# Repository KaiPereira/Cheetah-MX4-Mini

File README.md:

# Cheetah MX4 Mini Motherboard

The Cheetah MX4 Mini is a fully open source, powerful, yet affordable 3D printer motherboard! At just 80x90mm wide, it's an extremely compact motherboard with many cool features! This is one of the first PCB's I've ever created, so it might have some flaws.
## Custom Features
- 4 TMC stepstick drivers that support UART and SPI
- Sensorless and endstop homing configured using jumpers
- 3 Thermistor input connectors
- Support for parallel and serial LCD's and TFT displays
- 3 Fan output connectors
- Support for the BLTouch Probe (servo and probe connectors too)
- 2 High amperage heater outputs for a bed and miscellaneous
- Powerful STM32H743VIT6 LQFP100 MCU
- Support for USB-C and SD-Card printing
- 4x M3 grounded mounting holes
- Status and Power LEDs for programming
- 12/24V, 15A Input

## PCB Design

The Cheetah MX4 Mini is a 4 layer PCB with dedicated power and ground inner layers. Don't mind the messy PCB/schematic, it was one of my first boards ;) 

It's built off the STM32H series MCU to support every function you need for a printer. It's got many protection circuits, good decoupling, and is designed around high current inputs.

To power it, you can supply either USB-C for development, or a 12/24V PSU to drive the motors and all the other parts like the drivers.

You can upload prints via USB-C or SD Card, with support for UART and SPI TMC drivers, and you can hot-swap the motor drivers for maximum control.

## Firmware

The Cheetah MX4 Mini uses an STM32H743VIT6 MCU, so it has support for both Marlin, Klipper and most other 3D printer firmwares!

To get started, you can upload firmware to the onboard flash using the dedicated boot and reset pins!

More information on firmware *coming soon...*

## BOM (Bill of Materials)

I've created a BOM for JLCPCB and a general footprint BOM if you want to get PCBA from somewhere else like PCBWay or something.

The JLCPCB BOM is actually relatively cheap, coming in at about $150 for all 5 boards which I was pretty impressed with!

The LCSC BOM costs about $20 for the actual parts and then shipping will be about $20.

You can find the JLCPCB BOM [here](/production/BOM_JLCPCB.csv).

The LCSC BOM [here](/production/BOM_LCSC.csv)

The general footprint BOM is [here](/production/BOM.csv).

There's also a pick and place formatted for [JLCPCB](/production/CPL_JLCPCB.csv) and a general one if you're using a different platform [here](/production/CPL.csv).

## Credits

Thanks so much to @Fisheiyy and for the folks on Reddit for reviewing and helping me with the board, without them, this board probably would have never worked or come to fruition! Thanks also to Hackclub, specifically @qcoral and @acornitum for running [Highway](https://highway.hackclub.com/) which sponsored the board!

## License

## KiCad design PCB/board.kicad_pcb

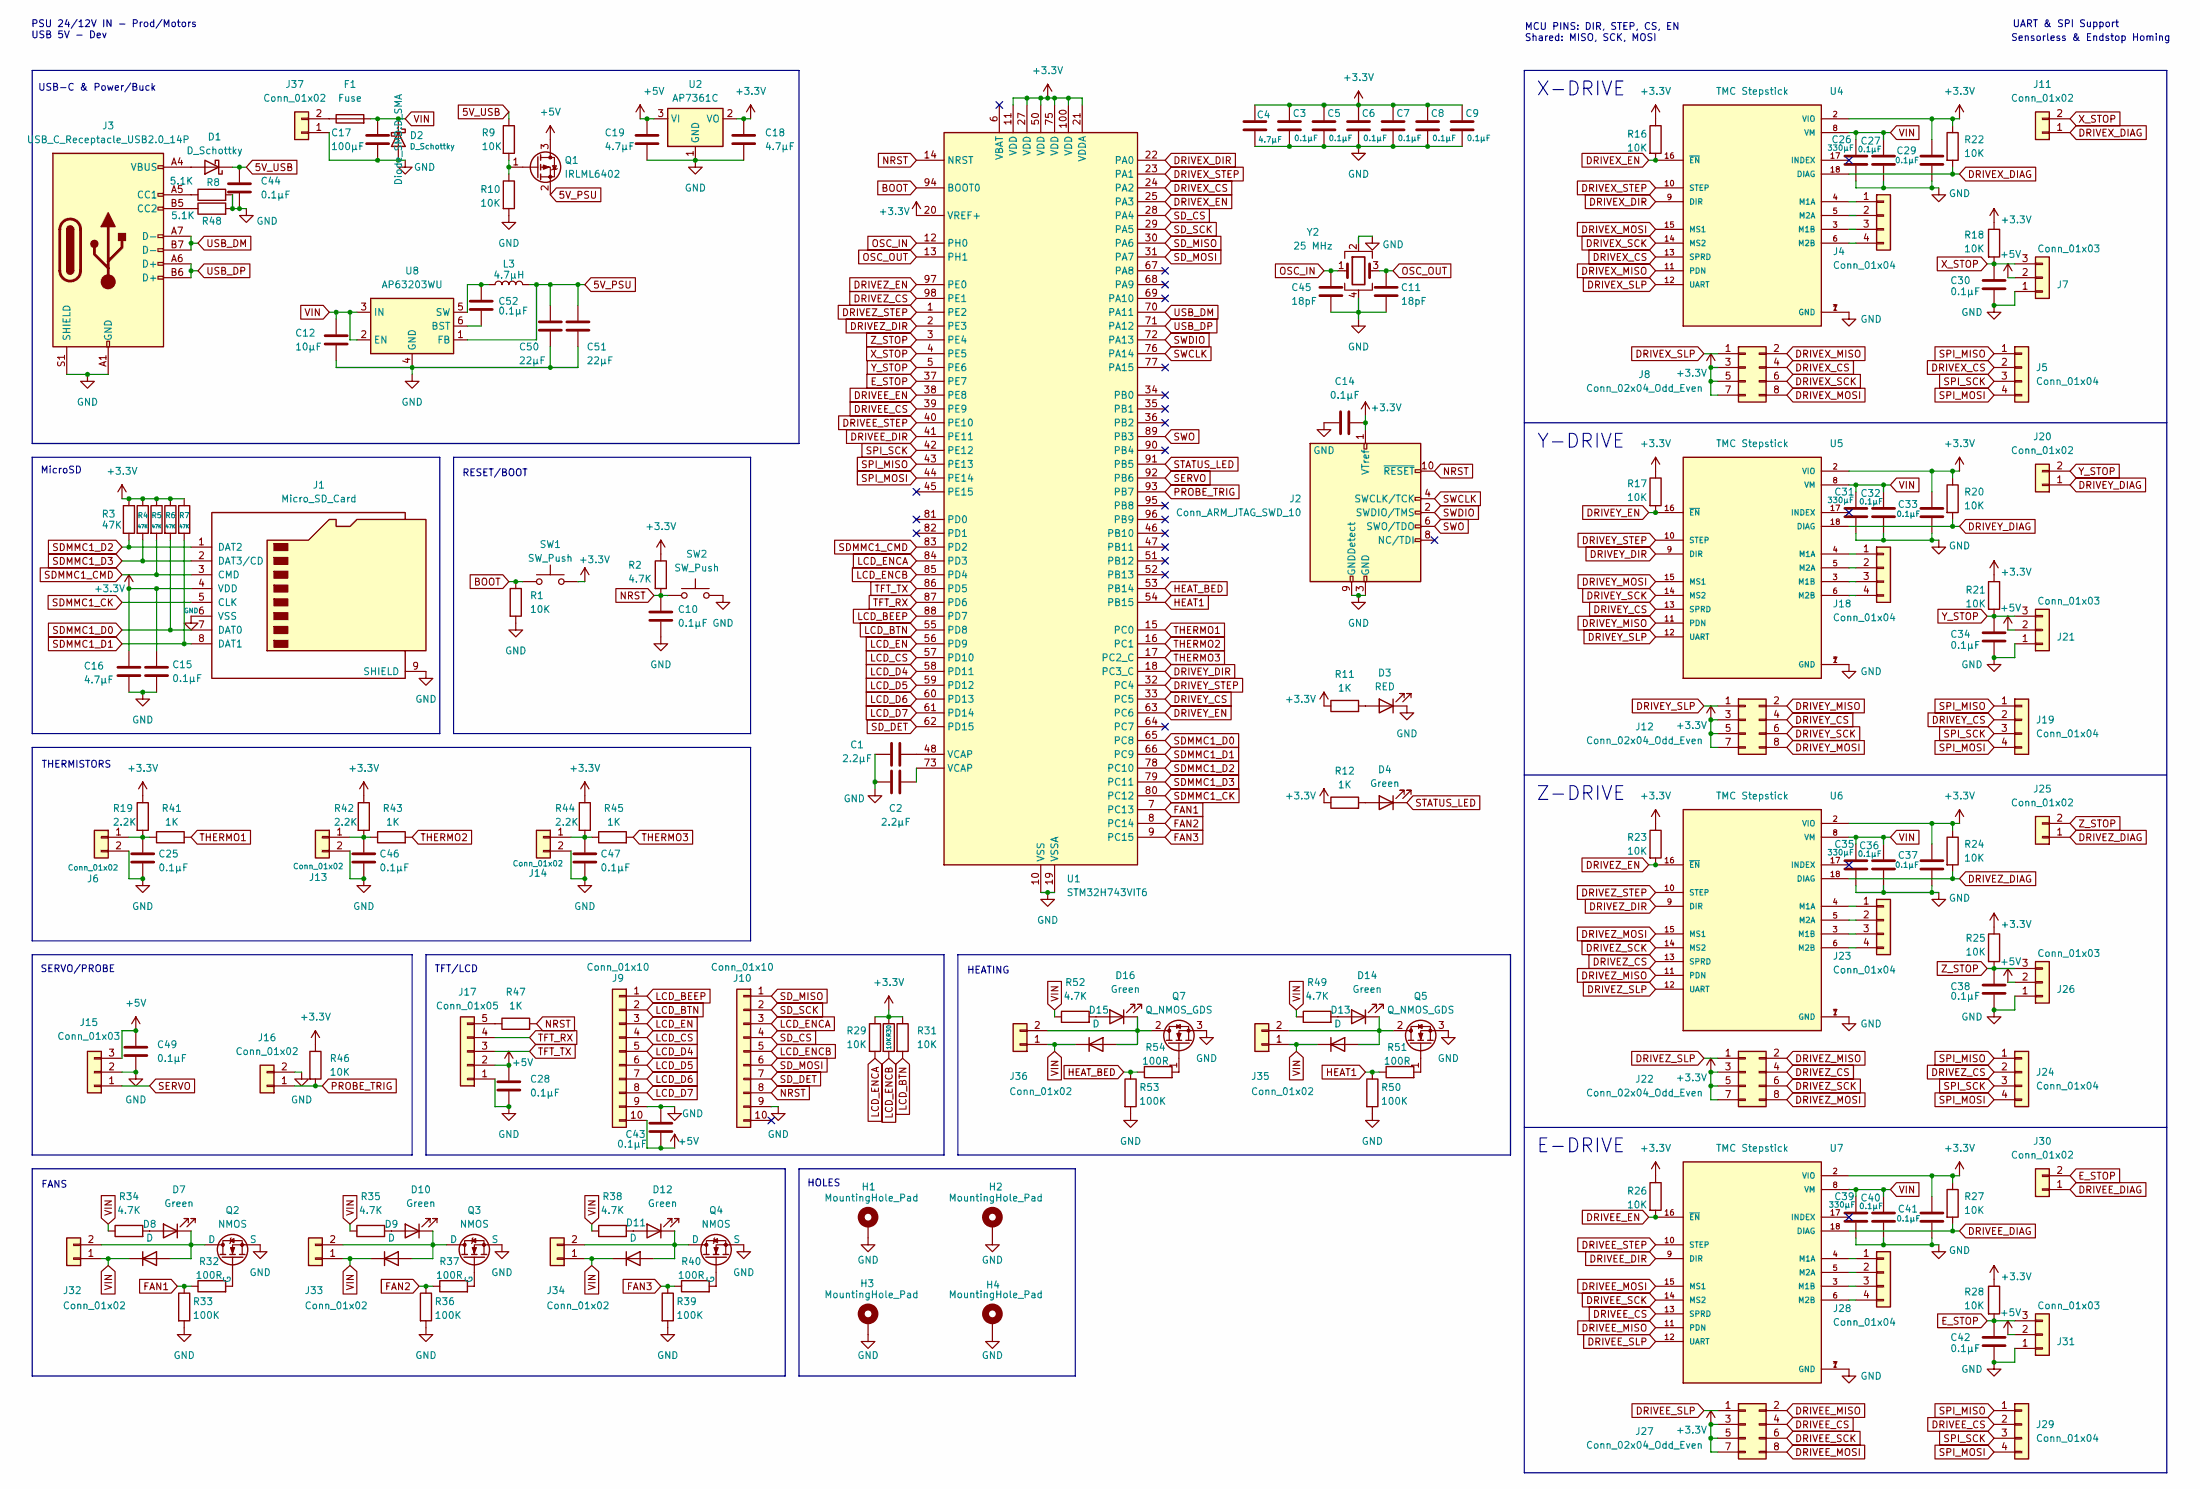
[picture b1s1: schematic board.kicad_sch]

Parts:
C1, C2: 2.2µF; C_0805_2012Metric
C3, C5, C6, C7, C8, C9, C10, C14, C15, C25, C27, C28, C29, C30, C32, C33, C34, C36, C37, C38, C40, C41, C42, C43, C44, C46, C47, C49, C52: 0.1µF; C_0603_1608Metric
C4, C16, C18, C19: 4.7µF; C_0805_2012Metric
C11, C45: 18pF; C_0603_1608Metric
C12: 10µF; C_0805_2012Metric
C17: 100µF; CP_Radial_D6.3mm_P2.50mm
C26, C31, C35, C39: 330µF; CP_Radial_D8.0mm_P3.50mm
C50, C51: 22µF; C_0805_2012Metric
D1: D_Schottky; D_SOD-123
D2: D_Schottky; D_SMA
D3: RED; LED_0805_2012Metric
D4, D7, D10, D12, D14, D16: Green; LED_0805_2012Metric
D8, D9, D11, D13, D15: D; D_SOD-123
F1: Fuse; Fuse_Blade_Mini_directSolder
H1, H2, H3, H4: MountingHole_Pad; MountingHole_3.2mm_M3_Pad_TopBottom
J1: Micro_SD_Card; microSD_HC_Hirose_DM3AT-SF-PEJM5
J2: Conn_ARM_JTAG_SWD_10; PinHeader_2x05_P1.27mm_Vertical
J3: USB_C_Receptacle_USB2.0_14P; USB_C_Receptacle_HRO_TYPE-C-31-M-12
J4, J18, J23, J28: Conn_01x04; JST_XH_B4B-XH-AM_1x04_P2.50mm_Vertical
J5, J19, J24, J29: Conn_01x04; PinHeader_1x04_P2.00mm_Vertical
J6, J13, J14, J32, J33, J34: Conn_01x02; JST_PH_B2B-PH-K_1x02_P2.00mm_Vertical
J7, J21, J26, J31: Conn_01x03; JST_XH_B3B-XH-A_1x03_P2.50mm_Vertical
J8, J12, J22, J27: Conn_02x04_Odd_Even; PinHeader_2x04_P2.00mm_Vertical
J9, J10: Conn_01x10; IDC-Header_2x05_P2.54mm_Vertical
J11, J16, J20, J25, J30: Conn_01x02; PinHeader_1x02_P2.54mm_Vertical
J15: Conn_01x03; PinHeader_1x03_P2.54mm_Vertical
J17: Conn_01x05; JST_XH_B5B-XH-AM_1x05_P2.50mm_Vertical
J35, J36, J37: Conn_01x02; TerminalBlock_Phoenix_MKDS-1,5-2-5.08_1x02_P5.08mm_Horizont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
L3: 4.7µH; L_Wuerth_HCM-7070
Q1: IRLML6402; SOT-23
Q2, Q3, Q4: NMOS; SOT-23-3
Q5, Q7: Q_NMOS_GDS; TO-252-3_TabPin2
R1, R9, R10, R16, R17, R18, R21, R23, R25, R26, R28, R29, R30, R31, R46: 10K; R_0603_1608Metric
R2, R34, R35, R38, R49, R52: 4.7K; R_0603_1608Metric
R3, R4, R5, R6, R7: 47K; R_0603_1608Metric
R8, R48: 5.1K; R_0603_1608Metric
R11, R12, R41, R43, R45, R47: 1K; R_0603_1608Metric
R19, R42, R44: 2.2K; R_0603_1608Metric
R20, R22, R24, R27: 10K; R_0805_2012Metric
R32, R37, R40, R51, R54: 100R; R_0603_1608Metric
R33, R36, R39, R50, R53: 100K; R_0603_1608Metric
SW1, SW2: SW_Push; SW_Push_1P1T_NO_CK_KMR2
U1: STM32H743VIT6; LQFP-100_14x14mm_P0.5mm
U2: AP7361C; SOT-223-3_TabPin2
U4, U5, U6, U7: TMC Stepstick; PARTREV 1.20
U8: AP63203WU; TSOT-23-6
Y2: 25 MHz; Crystal_SMD_3225-4Pin_3.2x2.5mm

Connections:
5V_PSU: C50.1, C51.1, L3.2, Q1.2 (S), U8.1 (FB)
5V_USB: C44.1, D1.1 (K), R9.1
+3.3V: C3.1, C4.1, C5.1, C6.1, C7.1, C8.1, C9.1, C14.2, C15.1, C16.1, C18.1, C29.1, C33.1, C37.1, C41.1, J1.4 (VDD), J2.1 (VTref), J8.3, J8.5, J8.7, J12.3, J12.5, J12.7, J22.3, J22.5, J22.7, J27.3, J27.5, J27.7, R2.1, R3.1, R4.1, R5.1, R6.1, R7.1, R11.1, R12.1, R16.1, R17.1, R18.1, R19.1, R20.1, R21.1, R22.1, R23.1, R24.1, R25.1, R26.1, R27.1, R28.1, R29.1, R30.1, R31.1, R42.1, R44.1, R46.1, SW1.2, U1.11 (VDD), U1.20 (VREF+), U1.21 (VDDA), U1.27 (VDD), U1.50 (VDD), U1.75 (VDD), U1.100 (VDD), U2.2 (VO), U4.2 (VIO), U5.2 (VIO), U6.2 (VIO), U7.2 (VIO)
+5V: C19.1, C28.1, C43.2, C49.1, J7.2, J9.10, J15.3, J17.2, J21.2, J26.2, J31.2, Q1.3 (D), U2.3 (VI)
BOOT: R1.1, SW1.1, U1.94 (BOOT0)
DRIVEE_CS: J27.4, J29.2, U1.39 (PE9), U7.13 (SPRD)
DRIVEE_DIAG: J30.1, R27.2, U7.18 (DIAG)
DRIVEE_DIR: U1.41 (PE11), U7.9 (DIR)
DRIVEE_EN: R26.2, U1.38 (PE8), U7.16 (~EN)
DRIVEE_MISO: J27.2, U7.11 (PDN)
DRIVEE_MOSI: J27.8, U7.15 (MS1)
DRIVEE_SCK: J27.6, U7.14 (MS2)
DRIVEE_SLP: J27.1, U7.12 (UART)
DRIVEE_STEP: U1.40 (PE10), U7.10 (STEP)
DRIVEX_CS: J5.2, J8.4, U1.24 (PA2), U4.13 (SPRD)
DRIVEX_DIAG: J11.1, R22.2, U4.18 (DIAG)
DRIVEX_DIR: U1.22 (PA0), U4.9 (DIR)
DRIVEX_EN: R16.2, U1.25 (PA3), U4.16 (~EN)
DRIVEX_MISO: J8.2, U4.11 (PDN)
DRIVEX_MOSI: J8.8, U4.15 (MS1)
DRIVEX_SCK: J8.6, U4.14 (MS2)
DRIVEX_SLP: J8.1, U4.12 (UART)
DRIVEX_STEP: U1.23 (PA1), U4.10 (STEP)
DRIVEY_CS: J12.4, J19.2, U1.33 (PC5), U5.13 (SPRD)
DRIVEY_DIAG: J20.1, R20.2, U5.18 (DIAG)
DRIVEY_DIR: U1.18 (PC3_C), U5.9 (DIR)
DRIVEY_EN: R17.2, U1.63 (PC6), U5.16 (~EN)
DRIVEY_MISO: J12.2, U5.11 (PDN)
DRIVEY_MOSI: J12.8, U5.15 (MS1)
DRIVEY_SCK: J12.6, U5.14 (MS2)
DRIVEY_SLP: J12.1, U5.12 (UART)
DRIVEY_STEP: U1.32 (PC4), U5.10 (STEP)
DRIVEZ_CS: J22.4, J24.2, U1.98 (PE1), U6.13 (SPRD)
DRIVEZ_DIAG: J25.1, R24.2, U6.18 (DIAG)
DRIVEZ_DIR: U1.2 (PE3), U6.9 (DIR)
DRIVEZ_EN: R23.2, U1.97 (PE0), U6.16 (~EN)
DRIVEZ_MISO: J22.2, U6.11 (PDN)
DRIVEZ_MOSI: J22.8, U6.15 (MS1)
DRIVEZ_SCK: J22.6, U6.14 (MS2)
DRIVEZ_SLP: J22.1, U6.12 (UART)
DRIVEZ_STEP: U1.1 (PE2), U6.10 (STEP)
E_STOP: C42.1, J30.2, J31.3, R28.2, U1.37 (PE7)
FAN1: R32.1, R33.1, U1.7 (PC13)
FAN2: R36.1, R37.1, U1.8 (PC14)
FAN3: R39.1, R40.1, U1.9 (PC15)
GND: C1.1, C2.1, C3.2, C4.2, C5.2, C6.2, C7.2, C8.2, C9.2, C10.2, C11.1, C12.2, C14.1, C15.2, C16.2, C17.2, C18.2, C19.2, C25.2, C26.2, C27.2, C28.2, C29.2, C30.2, C31.2, C32.2, C33.2, C34.2, C35.2, C36.2, C37.2, C38.2, C39.2, C40.2, C41.2, C42.2, C43.1, C44.2, C45.1, C46.2, C47.2, C49.2, C50.2, C51.2, D2.2 (A), D3.1 (K), H1.1, H2.1, H3.1, H4.1, J1.6 (VSS), J1.9 (SHIELD), J2.3 (GND), J2.5 (GND), J2.9 (GNDDetect), J3.A1 (GND), J3.A12 (GND), J3.B1 (GND), J3.B12 (GND), J3.S1 (SHIELD), J6.2, J7.1, J9.9, J10.9, J13.2, J14.2, J15.2, J16.2, J17.1, J21.1, J26.1, J31.1, J37.1, Q2.3 (S), Q3.3 (S), Q4.3 (S), Q5.3 (S), Q7.3 (S), R1.2, R8.2, R10.2, R33.2, R36.2, R39.2, R48.2, R50.2, R53.2, SW2.2, U1.10 (VSS), U1.19 (VSSA), U1.26 (VSS), U1.49 (VSS), U1.74 (VSS), U1.99 (VSS), U2.1 (GND), U4.1 (GND), U4.7 (GND), U5.1 (GND), U5.7 (GND), U6.1 (GND), U6.7 (GND), U7.1 (GND), U7.7 (GND), U8.4 (GND), Y2.2, Y2.4
HEAT1: R50.1, R51.1, U1.54 (PB15)
HEAT_BED: R53.1, R54.1, U1.53 (PB14)
LCD_BEEP: J9.1, U1.88 (PD7)
LCD_BTN: J9.2, R31.2, U1.55 (PD8)
LCD_CS: J9.4, U1.57 (PD10)
LCD_D4: J9.5, U1.58 (PD11)
LCD_D5: J9.6, U1.59 (PD12)
LCD_D6: J9.7, U1.60 (PD13)
LCD_D7: J9.8, U1.61 (PD14)
LCD_EN: J9.3, U1.56 (PD9)
LCD_ENCA: J10.3, R29.2, U1.84 (PD3)
LCD_ENCB: J10.5, R30.2, U1.85 (PD4)
NRST: C10.1, J2.10 (~RESET), J10.8, R2.2, R47.2, SW2.1, U1.14 (NRST)
unnamed: C1.2, U1.48 (VCAP)
unnamed: C2.2, U1.73 (VCAP)
unnamed: D1.2 (A), J3.A4 (VBUS), J3.A9 (VBUS), J3.B4 (VBUS), J3.B9 (VBUS)
unnamed: D3.2 (A), R11.2
unnamed: D4.2 (A), R12.2
unnamed: D7.2 (A), R34.2
unnamed: D7.1 (K), D8.2 (A), J32.2, Q2.1 (D)
unnamed: D10.2 (A), R35.2
unnamed: D9.2 (A), D10.1 (K), J33.2, Q3.1 (D)
unnamed: D11.2 (A), D12.1 (K), J34.2, Q4.1 (D)
unnamed: D12.2 (A), R38.2
unnamed: D13.2 (A), D14.1 (K), J35.2, Q5.2 (D)
unnamed: D14.2 (A), R49.2
unnamed: D15.2 (A), D16.1 (K), J36.2, Q7.2 (D)
unnamed: D16.2 (A), R52.2
unnamed: J3.A5 (CC1), R8.1
unnamed: J3.B5 (CC2), R48.1
unnamed: J4.1, U4.4 (M1A)
unnamed: J4.2, U4.5 (M2A)
unnamed: J4.3, U4.3 (M1B)
unnamed: J4.4, U4.6 (M2B)
unnamed: C25.1, J6.1, R19.2, R41.1
unnamed: C46.1, J13.1, R42.2, R43.1
unnamed: C47.1, J14.1, R44.2, R45.1
unnamed: J17.5, R47.1
unnamed: J18.1, U5.4 (M1A)
unnamed: J18.2, U5.5 (M2A)
unnamed: J18.3, U5.3 (M1B)
unnamed: J18.4, U5.6 (M2B)
unnamed: J23.1, U6.4 (M1A)
unnamed: J23.2, U6.5 (M2A)
unnamed: J23.3, U6.3 (M1B)
unnamed: J23.4, U6.6 (M2B)
unnamed: J28.1, U7.4 (M1A)
unnamed: J28.2, U7.5 (M2A)
unnamed: J28.3, U7.3 (M1B)
unnamed: J28.4, U7.6 (M2B)
unnamed: F1.1, J37.2
unnamed: Q1.1 (G), R9.2, R10.1
unnamed: Q2.2 (G), R32.2
unnamed: Q3.2 (G), R37.2
unnamed: Q4.2 (G), R40.2
unnamed: Q5.1 (G), R51.2
unnamed: Q7.1 (G), R54.2
unnamed: C52.2, U8.6 (BST)
unnamed: C52.1, L3.1, U8.5 (SW)
OSC_IN: C45.2, U1.12 (PH0), Y2.1
OSC_OUT: C11.2, U1.13 (PH1), Y2.3
PROBE_TRIG: J16.1, R46.2, U1.93 (PB7)
SDMMC1_CK: J1.5 (CLK), U1.80 (PC12)
SDMMC1_CMD: J1.3 (CMD), R5.2, U1.83 (PD2)
SDMMC1_D0: J1.7 (DAT0), R6.2, U1.65 (PC8)
SDMMC1_D1: J1.8 (DAT1), R7.2, U1.66 (PC9)
SDMMC1_D2: J1.1 (DAT2), R3.2, U1.78 (PC10)
SDMMC1_D3: J1.2 (DAT3/CD), R4.2, U1.79 (PC11)
SD_CS: J10.4, U1.28 (PA4)
SD_DET: J10.7, U1.62 (PD15)
SD_MISO: J10.1, U1.30 (PA6)
SD_MOSI: J10.6, U1.31 (PA7)
SD_SCK: J10.2, U1.29 (PA5)
SERVO: J15.1, U1.92 (PB6)
SPI_MISO: J5.1, J19.1, J24.1, J29.1, U1.43 (PE13)
SPI_MOSI: J5.4, J19.4, J24.4, J29.4, U1.44 (PE14)
SPI_SCK: J5.3, J19.3, J24.3, J29.3, U1.42 (PE12)
STATUS_LED: D4.1 (K), U1.91 (PB5)
SWCLK: J2.4 (SWCLK/TCK), U1.76 (PA14)
SWDIO: J2.2 (SWDIO/TMS), U1.72 (PA13)
SWO: J2.6 (SWO/TDO), U1.89 (PB3)
TFT_RX: J17.4, U1.87 (PD6)
TFT_TX: J17.3, U1.86 (PD5)
THERMO1: R41.2, U1.15 (PC0)
THERMO2: R43.2, U1.16 (PC1)
THERMO3: R45.2, U1.17 (PC2_C)
USB_DM: J3.A7 (D-), J3.B7 (D-), U1.70 (PA11)
USB_DP: J3.A6 (D+), J3.B6 (D+), U1.71 (PA12)
VIN: C12.1, C17.1, C26.1, C27.1, C31.1, C32.1, C35.1, C36.1, C39.1, C40.1, D2.1 (K), D8.1 (K), D9.1 (K), D11.1 (K), D13.1 (K), D15.1 (K), F1.2, J32.1, J33.1, J34.1, J35.1, J36.1, R34.1, R35.1, R38.1, R49.1, R52.1, U4.8 (VM), U5.8 (VM), U6.8 (VM), U7.8 (VM), U8.2 (EN), U8.3 (IN)
X_STOP: C30.1, J7.3, J11.2, R18.2, U1.4 (PE5)
Y_STOP: C34.1, J20.2, J21.3, R21.2, U1.5 (PE6)
Z_STOP: C38.1, J25.2, J26.3, R25.2, U1.3 (PE4)

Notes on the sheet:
PSU 24/12V IN - Prod/Motors USB 5V - Dev
MicroSD
Y-DRIVE
UART & SPI Support
SERVO/PROBE
HOLES
Z-DRIVE
THERMISTORS
USB-C & Power/Buck
X-DRIVE
TFT/LCD
MCU PINS: DIR, STEP, CS, EN Shared: MISO, SCK, MOSI
HEATING
E-DRIVE
Sensorless & Endstop Homing
FANS
RESET/BOOT

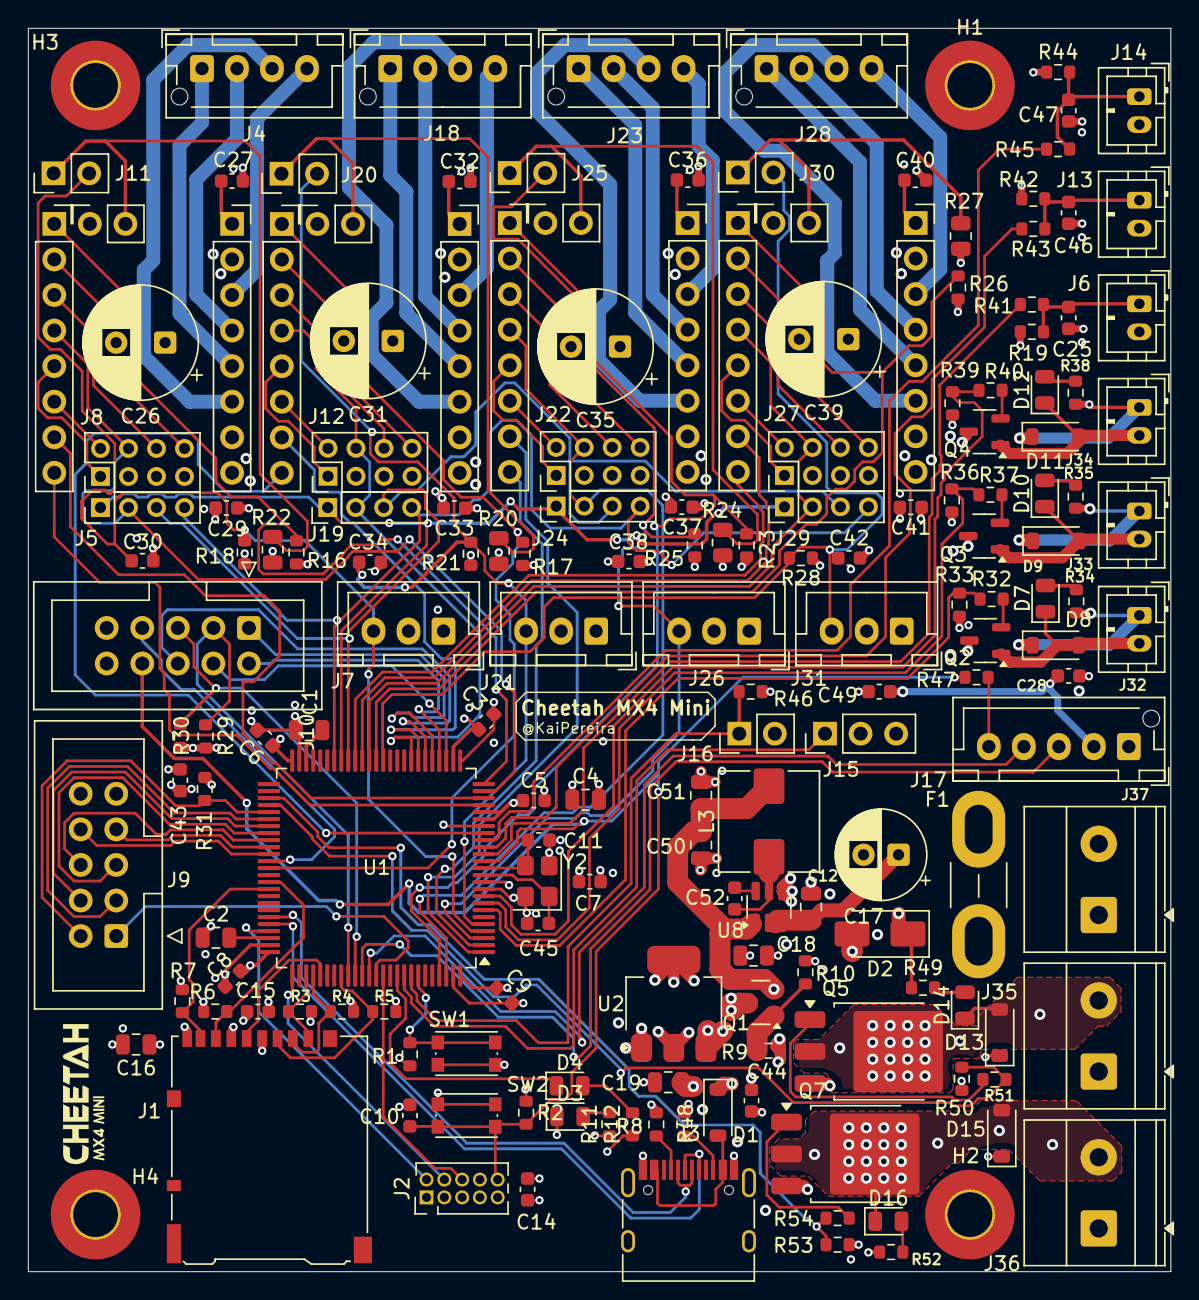
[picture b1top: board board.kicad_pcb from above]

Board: 4 copper layers, 81.6 x 88.8 mm, 169 parts (0 on the bottom side), 138 nets.

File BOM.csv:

"Id";"Designator";"Footprint";"Quantity";"Designation";"Supplier and ref";
1;"C51,C50";"C_0805_2012Metric";2;"22µF";;;
2;"R33,R39,R36,R50,R53";"R_0603_1608Metric";5;"100K";;;
3;"Q7,Q5";"TO-252-3_TabPin2";2;"Q_NMOS_GDS";;;
4;"C45,C11";"C_0603_1608Metric";2;"18pF";;;
5;"C15,C27,C7,C43,C40,C6,C32,C46,C28,C49,C8,C29,C3,C36,C10,C52,C37,C33,C30,C25,C38,C42,C34,C14,C9,C41,C47,C44,C5";"C_0603_1608Metric";29;"0.1µF";;;
6;"R10,R26,R25,R18,R21,R16,R1,R30,R28,R29,R31,R46,R9,R17,R23";"R_0603_1608Metric";15;"10K";;;
7;"J2";"PinHeader_2x05_P1.27mm_Vertical_SMD";1;"Conn_ARM_JTAG_SWD_10";;;
8;"J19,J29,J24,J5";"PinHeader_1x04_P2.00mm_Vertical";4;"Conn_01x04";;;
9;"J12,J27,J22,J8";"PinHeader_2x04_P2.00mm_Vertical";4;"Conn_02x04_Odd_Even";;;
10;"C19,C18,C16,C4";"C_0805_2012Metric";4;"4.7µF";;;
11;"J4,J28,J18,J23";"JST_XH_B4B-XH-AM_1x04_P2.50mm_Vertical";4;"Conn_01x04";;;
12;"SW2,SW1";"SW_Push_1P1T_NO_CK_KMR2";2;"SW_Push";;;
13;"R49,R2,R34,R35,R38,R52";"R_0603_1608Metric";6;"4.7K";;;
14;"L3";"L_Wuerth_HCM-7070";1;"4.7µH";;;
15;"J11,J30,J20,J16,J25";"PinHeader_1x02_P2.54mm_Vertical";5;"Conn_01x02";;;
16;"D10,D7,D16,D12,D14";"R_0805_2012Metric";5;"Green";;;
17;"R40,R51,R37,R32,R54";"R_0603_1608Metric";5;"100R";;;
18;"U2";"SOT-223-3_TabPin2";1;"AP7361C";;;
19;"U5,U7,U4,U6";"TMC Stepstick";4;"TMC Stepstick";;;
20;"D1";"D_SOD-123";1;"D_Schottky";;;
21;"R20,R27,R22,R24";"R_0805_2012Metric";4;"10K";;;
22;"J13,J14,J33,J6,J34,J32";"JST_PH_B2B-PH-K_1x02_P2.00mm_Vertical";6;"Conn_01x02";;;
23;"U1";"LQFP-100_14x14mm_P0.5mm";1;"STM32H743VITx";;;
24;"R7,R3,R4,R6,R5";"R_0603_1608Metric";5;"47K";;;
25;"R47,R45,R43,R41";"R_0603_1608Metric";4;"1K";;;
26;"Q3,Q4,Q2";"SOT-23-3";3;"NMOS";;;
27;"U8";"TSOT-23-6";1;"AP63203WU";;;
28;"J36,J37,J35";"TerminalBlock_Phoenix_MKDS-1,5-2-5.08_1x02_P5.08mm_Horizontal";3;"Conn_01x02";;;
29;"D2";"D_SMA";1;"D_Schottky";;;
30;"C39,C31,C35,C26";"CP_Radial_D8.0mm_P3.50mm";4;"330µF";;;
31;"D13,D15,D9,D8,D11";"D_SOD-123";5;"D";;;
32;"J26,J7,J31,J21";"JST_XH_B3B-XH-A_1x03_P2.50mm_Vertical";4;"Conn_01x03";;;
33;"J17";"JST_XH_B5B-XH-AM_1x05_P2.50mm_Vertical";1;"Conn_01x05";;;
34;"R48,R8";"R_0603_1608Metric";2;"5.1K";;;
35;"F1";"Fuse_Blade_Mini_directSolder";1;"Fuse";;;
36;"J1";"microSD_HC_Hirose_DM3AT-SF-PEJM5";1;"Micro_SD_Card";;;
37;"R44,R42,R19";"R_0603_1608Metric";3;"2.2K";;;
38;"J15";"PinHeader_1x03_P2.54mm_Vertical";1;"Conn_01x03";;;
39;"J3";"USB_C_Receptacle_HRO_TYPE-C-31-M-12";1;"USB_C_Receptacle_USB2.0_14P";;;
40;"C12";"C_0805_2012Metric";1;"10µF";;;
41;"J9,J10";"IDC-Header_2x05_P2.54mm_Vertical";2;"Conn_01x10";;;
42;"C17";"CP_Radial_D6.3mm_P2.50mm";1;"100µF";;;
43;"C2,C1";"C_0805_2012Metric";2;"2.2µF";;;
44;"Y2";"Crystal_SMD_3225-4Pin_3.2x2.5mm";1;"25 MHz";;;
45;"Q1";"SOT-23";1;"IRLML6402";;;

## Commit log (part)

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2025-07-20 started project, this is probably a bad idea lol
2025-07-20 everything so far
2025-07-21 added PCB files again
2025-07-21 started the schematic, I still think this is a horrible idea, but it's going to be so cool
2025-07-21 adding decoupling caps to VDD
2025-07-21 adding boot and fixed the decoupling
2025-07-21 danny helped me with my PCB :D
2025-07-21 working on NRST
2025-07-21 separate the boot/reset schematic into a little box!
2025-07-21 added crystal oscillator
2025-07-21 added clock stuff and updated my journal
2025-07-21 adding ferrite bead to VDD
2025-07-21 adding my SWD debugger headers, I think I'm using the wrong symbol though
2025-07-22 adding the SD card
2025-07-22 connected shield to GND and updated journal with SD card
2025-07-22 adding usb-c in progress
2025-07-22 usb-c is done I think
2025-07-22 forgot to save USB-C, but I did that, and I also wrote about it in the journal
2025-07-22 saved
2025-07-22 formatting the schematic a bit better
2025-07-22 adding psu
2025-07-22 psu stuff
2025-07-22 added psu circuit
2025-07-22 added buck converter
2025-07-22 adding journal for PSU and buck converter
2025-07-23 added the new buck converter but the schematic looks a tad messy and the value's aren't in eyt
2025-07-23 switching power net labels to power labels
2025-07-23 added new buck converter
2025-07-23 added new blog for the buck converter
2025-07-23 added LDO
2025-07-24 P-Mosfet for PSU/USB switching and added the LDO
2025-07-24 added a new TMC symbol from snapeda
2025-07-24 added stepstick driver, I think it's fine, but I'm not too sure
2025-07-24 re-organized the schematic and bit more and did the journal for the stepper
2025-07-24 added the endstop, but now I have to implement both sensorless and endstop home
2025-07-24 added endstop connectors and started working on footprints and stuff which was dumb not to do initially, also already added the journal log
2025-07-24 fixing the TMC2209 stepstick, I was wiring it like the IC, not the module for some reason and it was a bit off in general
2025-07-24 added decoupling caps to power pins on drivers
2025-07-24 added some thermistor stuff and re-organized a bit
2025-07-25 fixed the UART on the drivers
2025-07-25 sd card peripheral was messed up for some reason
2025-07-25 added all motor drivers in (x, y, z, e0)
2025-07-25 updated the journal on adding all the motor drivers in
2025-07-25 added in the first thermistor with protection
2025-07-25 adding all the thermistors
2025-07-25 adding the journal for the rest of the thermistors
2025-07-25 added the servo connector
2025-07-25 added probe stuff
2025-07-25 fixed some dumb language mistakes
2025-07-25 fixed usb cc pin not pulled down and lower bulk capacitance cap on the PSU
2025-07-25 fixing capacitors on the motor drivers, removed the other drivers while making edits
2025-07-25 fixed pullups on thermistors
2025-07-26 finally fixed the UART on my drivers! Thanks salmon :D
2025-07-26 added some SPI peripherals on
2025-07-26 working on more SPI stuff, working on jumpers
2025-07-26 I might crash out from SPI but this MIGHT be fine?
2025-07-26 refining the SPI a bit
2025-07-26 added all the drivers, but haven't named them yet
2025-07-26 kind of going insane, but I can't figure out how UART is getting a signal??
2025-07-27 added SPI to journal
2025-07-27 adding TFT to journal and fixing it up on the schematic
2025-07-27 adding the SPI/sd card display support
2025-07-27 added some stuff
2025-07-27 wired up some more stuff for the LCD's
2025-07-27 re-doing some driver pins because I keep on messing them up
2025-07-27 adding the endstop jumper to switch between sensorless and endstop
2025-07-27 almost everything wired on the TMC drivers
2025-07-27 some more formatting, almost done adding all the io's for the drivers
2025-07-27 that might be all the labels in the right spots for the drivers?
2025-07-27 updated the journal with all the stuff I did
2025-07-27 some more journaling stuff and pullups on LCD
2025-07-27 updated the journal and added some decoupling to LCD's
2025-07-27 working on fan
2025-07-27 added fans to journal
2025-07-27 added the heating outputs
2025-07-27 added the journal for the heating elements
2025-07-27 footprints for usb
2025-07-27 added footprints to the PSU
2025-07-27 footprints for psu
2025-07-27 sd card footprints
2025-07-27 added the footprints for the thermistors
2025-07-27 most of the capacitors using assign footprints
2025-07-27 some more footprints
2025-07-27 A LOT more footprint stuff
2025-07-28 even more footprints
2025-07-28 more footpritns, I should've done this while making the schematic...
2025-07-28 adding some more footprints
2025-07-28 all the driver connectors
2025-07-28 ALL the footprints except for the TMC stepsticks
2025-07-28 formatted the entire schematic much more nicely
2025-07-28 added all the stuff
2025-07-28 added journal for footprint
2025-07-28 added TMC footprint to the drivers
2025-07-28 changed some footprints to handle the loads
2025-07-28 fixing the footprint for the motor drivers
2025-07-28 fixed all the connectors except the LCD/TFT ones
2025-07-29 added the display connectors, finally!
2025-07-29 simplifying the BOM
2025-07-29 cleaner up some stuff, this would be a good commit to revert too
2025-07-29 moving the fuse before cap and diode
2025-07-29 making the diodes less overkill
2025-07-29 started working on the PCB
2025-07-29 working on the PCB!
2025-07-29 currently aligning all the parts for the pcb
2025-07-29 organized thermistors
2025-07-29 boot/reset and power organization
2025-07-29 everything organized on the board together, now I just have to precisely put it on, but I gotta figure out the screens first
2025-07-29 updated sd card, at least I think that was the change?
2025-07-29 changed the buttons
2025-07-29 switched symbol to receptacle instead of plug for usb-c
2025-07-29 started organizing the mcu more precisely
2025-07-29 fixed the crystal pins
2025-07-29 fixed up the mcu footprint some more
2025-07-29 added the current pcb stuff to the journal
2025-07-29 fixing the connector size on the UART/SPI toggle
2025-07-29 starting to organize the drivers nicely
2025-07-29 third driver
2025-07-29 fourth driver
2025-07-29 aligned all the motor drivers together
2025-07-29 added the driver alignement to journal
2025-07-29 lots of organizing the power and displays
2025-07-29 hopping off cuz it's 3am...
2025-07-29 fixed the buck converter
2025-07-29 new LDO and fixed decoup
2025-07-29 don't go to this commit, can't figure out 5V mosfet switching?
2025-07-29 added the power switching
2025-07-29 schematic looks golden now!
2025-07-29 added the schematic changes to the journal
2025-07-30 organizing everything into a more coherent board
2025-07-30 much better organization of the pcb
2025-07-30 organized fan connectors
2025-07-30 heaters
2025-07-30 all components place all organized
2025-07-30 added the organization stuff to the journal
2025-07-30 re-oriented, this is a good version to go to
2025-07-30 starting to compress everything now, motor drivers and mcu down
2025-07-30 compressing stuff
2025-07-30 compressing even more stuff, specifically the power stuff
2025-07-30 some major changes to placement
2025-07-30 trying a slightly different layout
2025-07-30 updated journal, but I need to fix the NMOS on the heaters
2025-07-30 changing the FET/Mosfet
2025-07-30 forgot to save board
2025-07-30 everything is on nicely, but I may or may not have forgotten mounting holes
2025-07-30 the board is almost ready to route! Good place to backup too
2025-07-30 fixed the mosfets on the heaters
2025-07-31 adding mounting holes
2025-07-31 first round of mounting holes
2025-07-31 ALL mounting holes placed down
2025-07-31 fine tuning some stuff
2025-07-31 some journal stuff and starting the routing
2025-07-31 started to via all the grounds down
2025-07-31 organized like over half the silkscreen
2025-07-31 progress so far
2025-07-31 started routing some stuff
2025-07-31 added some more routes
2025-07-31 lots more wiring
2025-07-31 filled the heaters a bit
2025-07-31 update journal for the routing
2025-07-31 routing the drivers
2025-07-31 routed a display and more stuff on the drivers + journal
2025-07-31 removing redundant stuff in the schematic and some more routing
2025-07-31 some more mcu routing
2025-07-31 hopping off for the night, very good progress though!
2025-07-31 re-formatting the layout
2025-07-31 updated journal with new layout
2025-07-31 routing the mcu some more
2025-07-31 some thermistor routing
2025-07-31 re-wired the crystal
2025-07-31 properly routed the sd card
2025-07-31 added lots of mcu signal traces and journal stuff
2025-07-31 a bunch more routing
2025-08-01 I think that's all the signal pins
2025-08-01 going to start working on power now
2025-08-01 working on power rails
2025-08-01 more power and routing
2025-08-01 only 23 unconnected pads left!
2025-08-01 so far
2025-08-01 only 9 drc errors left!
2025-08-01 almost done the board! Just 6 unconnected items
2025-08-01 only 2 drc errors left!
2025-08-01 finished the PCB (well no drc errors
2025-08-01 fixing images in the journal
2025-08-01 started the README
2025-08-01 some more readme stuff
2025-08-01 fixing readme images
2025-08-01 added production files
2025-08-01 added a 3D model to the models folder for fun
2025-08-01 adding some pickk and place files
2025-08-01 FMAKING THE INDUCTOR ROUTING BETTER, not adding prod files yet tho, cuz tenting first
2025-08-01 moved the spi/uart driver jumpers a bit
2025-08-01 updated footprints for the stepsticks
2025-08-01 fixing 3D models
2025-08-01 adding ground fills to every layer
2025-08-02 some more thermal reliefs
2025-08-02 removing via's on pads
2025-08-02 removing via's on pads some more
2025-08-03 removing all via's on pads
2025-08-03 removed more pads from via's
2025-08-03 almost done with all the via's in pads
2025-08-03 no more via's on pads (except on mosfets) and re-did mosfet fills for both layers
2025-08-03 added proper stiching to the heater mosfets
2025-08-03 redoing my ground stiching again!
2025-08-03 finishing the ground stiching
2025-08-03 re-orienting silkscreen so all of it is visible!
2025-08-03 all silkscreen should be visible now!
2025-08-04 added some silkscreen to the board
2025-08-04 removing debug header with THT one
2025-08-04 updating schematic with new debug header
2025-08-05 updating 3d model for tmc drivers
2025-08-05 ACTUALLY updating the 3d models now
2025-08-05 working on renders
2025-08-05 updating the USB-C model on the pcb
2025-08-05 new pcb3d model onow
2025-08-05 new basic render
2025-08-05 big pprogress on the render
2025-08-05 rendered my project!
2025-08-05 renaming some stuff
2025-08-05 work so far on renders
2025-08-05 fixing the BOM
2025-08-05 updated the pick and place
2025-08-05 reformating to be clean and JLCPCB compatible
2025-08-05 removing and renaming some files
2025-08-06 current BOM so far!
2025-08-06 added a status LED
2025-08-06 updating footprints for ALl the led's
2025-08-06 updating pcb with the new LED's
2025-08-06 fixing pcb drc errors
2025-08-06 updating prod files
2025-08-06 updated the cpl for jlcpcb formatting
2025-08-07 added a jlcpcb BOM
2025-08-07 new BOM with unselected items
2025-08-07 updating journal
2025-08-07 updating readme for OBM
2025-08-07 update readme again
2025-08-07 update readme with cpl's
2025-08-07 updating the readme with new photo's
2025-08-07 added firmware boilerplate so reviewers don't get mad :3
2025-08-08 Updating readme features
2025-08-10 updated BOM
2025-08-11 I may be on vacation, but I'm getting this PCB done and dusted!
2025-08-11 fixing some of the cap placements
2025-08-11 update repo for PCBA, for some reason I had corrupt git files
2025-08-14 updating BOM
2025-08-14 update files
2025-08-14 re-adding OG BOM
2025-08-15 update repo
2025-08-15 added an LCSC BOM
2025-08-15 renaming the BOM file cuz it's bothering me...
2025-09-07 update pdf
2025-09-08 add license
2025-11-16 added the real photo!
2025-11-16 making the photo a bit smaller so it renders faster!
2025-11-16 Changing readme image to real photo :D
2025-11-16 Added credits to highway and alex/acon :D
2025-11-22 Update main image in my readme!
2025-11-23 adding the real image to the repo!
2025-11-23 Revising the readme!
2025-11-23 Revising readme!
2025-12-06 Modifying the journal!
